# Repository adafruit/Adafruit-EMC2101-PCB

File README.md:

## Adafruit EMC2101 Tempature Sensor and Fan Controller PCB

<a href="http://www.adafruit.com/products/4808"><br/>
Click here to purchase one from the Adafruit shop</a>

PCB files for the Adafruit EMC2101 Tempature Sensor and Fan Controller. 

Format is EagleCAD schematic and board layout
* https://www.adafruit.com/product/4808

### Description

Cooling fans. They're everywhere, and they serve the important purpose of keeping things cool, generally electronics. One might rightfully think: "these fans are pretty good at moving air to keep things cool; maybe I can use one of these neat computer fans to keep my widget frosty" followed closely by throwing up one's hands in confusion at the sight of a 3 or even 4-pin connector. OK, power takes two pins but what are these other pins for and how do I use them to convince this fan to keep my things chilly?

The EMC2101 from Microchip/SMSC is a 1 degree C accurate fan controller with temperature monitoring and it will take care of all of that for you. Those extra pins allow you to set a the speed of the fan, and in the additional pin of a 4-pin connector adds a tachometer output that allows you (or the EMC2101) to monitor the speed of the fan to make sure it's working as expected. In addition to allowing you to control a fan, the EMC2101 includes an internal temperature sensor, as well as connections for an external temperature sensing diode. If you use an external temperature sensor, you can even configure a look up table (LUT) that allows you to set different fan speeds depending on the temperature, and the EMC2101 will automatically adjust the speed depending on the temperature.

This neat little chip can easily be used to help provide cooling or ventilation to your next project. You might even be able to use it to help quiet down an existing project or hack a noisy piece of electronics that has a loud fan. By allowing you to run a fan at slower speeds when cooling needs are moderate, the EMC2101 can help ease the noise pollution caused by fans running at full speed.

Delivered to you on our custom Stemma QT form factor PCB, the Adafruit EMC2101 breakout is ready to help you integrate a fan into your project by making it easy to use with a range of devices. A voltage regulator and 5V tolerant pins allow you to use it with 3.3V or 5V microcontrollers or single board computers. The included included SparkFun qwiic compatible STEMMA QT connectors for the I2C bus allow you to make easy solderless connections to your controlling device, and the standard headers make breadboard prototyping easy.Our libraries, wiring diagrams, and example code for Arduino, CircuitPython and Python complete the package. Fantastic!

### License

Adafruit invests time and resources providing this open source design, please support Adafruit and open-source hardware by purchasing products from [Adafruit](https://www.adafruit.com)!

Designed by Limor Fried/Ladyada for Adafruit Industries.

Creative Commons Attribution/Share-Alike, all text above must be included in any redistribution. 
See license.txt for additional details.

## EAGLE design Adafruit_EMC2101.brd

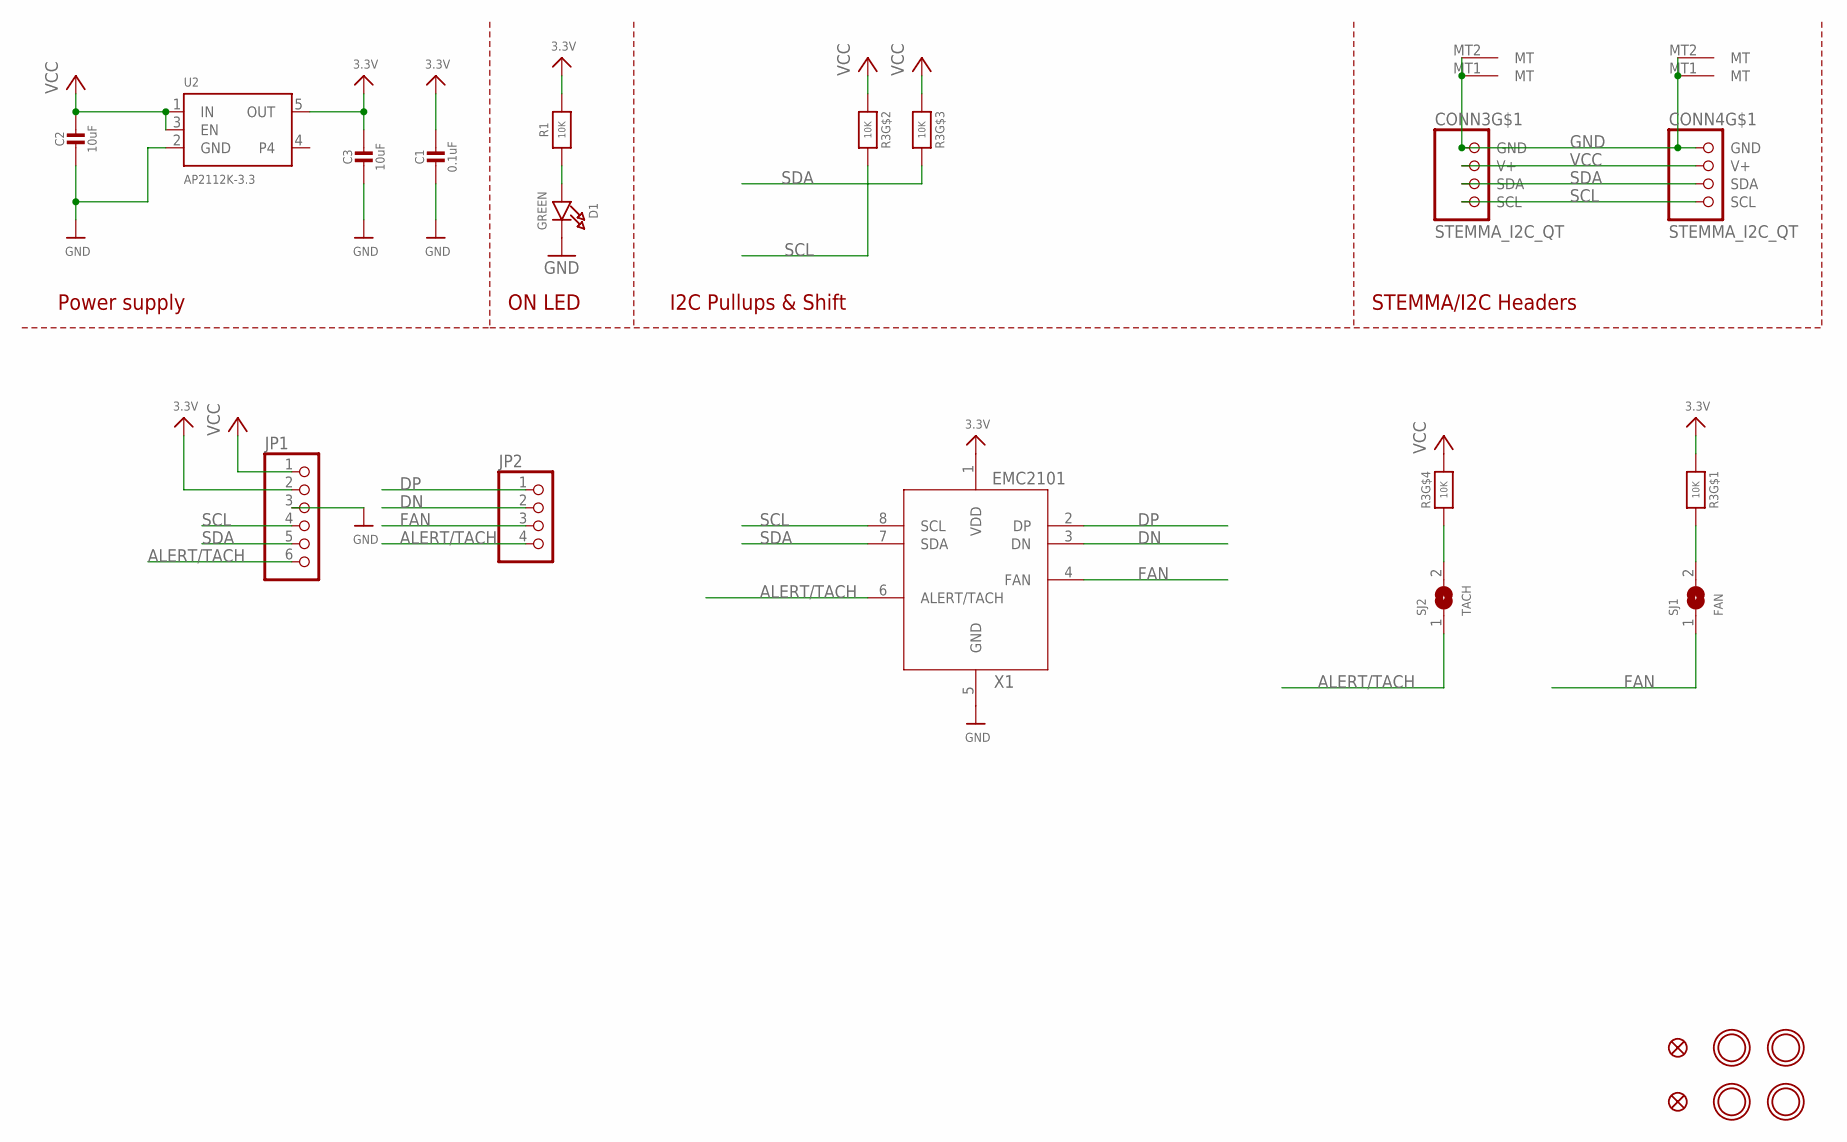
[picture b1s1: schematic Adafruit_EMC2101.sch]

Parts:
C1: 0.1uF; 0603-NO
C2, C3: 10uF; 0805-NO
CONN3, CONN4: STEMMA_I2C_QT; JST_SH4
D1: GREEN; CHIPLED_0603_NOOUTLINE
FID3, FID4: FIDUCIAL_1MM
JP1: HEADER-1X670MIL; 1X06_ROUND_70
JP2: HEADER-1X4ROUND; 1X04_ROUND
R1: 10K; _0603MP
R3: 10K; RESPACK_4X0603
SJ1: FAN; SOLDERJUMPER_CLOSEDWIRE
SJ2: TACH; SOLDERJUMPER_ARROW_NOPASTE
U2: AP2112K-3.3; SOT23-5
U$1, U$17, U$19, U$21: MOUNTINGHOLE2.5; MOUNTINGHOLE_2.5_PLATED
X1: EMC2101-AZCL; MSOP8_0.65MM

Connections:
3.3V: C1.1, C3.1, JP1.2, R1.2, R3.1, U2.5 (OUT), X1.1 (VDD)
ALERT/TACH: JP1.6, JP2.4, SJ2.1, X1.6 (ALERT/TACH)
DN: JP2.2, X1.3 (DN)
DP: JP2.1, X1.2 (DP)
FAN: JP2.3, SJ1.1, X1.4 (FAN)
GND: C1.2, C2.2, C3.2, CONN3.1 (GND), CONN3.MT1 (MT), CONN3.MT2 (MT), CONN4.1 (GND), CONN4.MT1 (MT), CONN4.MT2 (MT), D1.C, JP1.3, U2.2 (GND), X1.5 (GND)
unnamed: R3.4 (1), SJ2.2
unnamed: R3.8 (2), SJ1.2
unnamed: D1.A, R1.1
SCL: CONN3.4 (SCL), CONN4.4 (SCL), JP1.4, R3.7 (2), X1.8 (SCL)
SDA: CONN3.3 (SDA), CONN4.3 (SDA), JP1.5, R3.6 (2), X1.7 (SDA)
VCC: C2.1, CONN3.2 (V+), CONN4.2 (V+), JP1.1, R3.2 (1), R3.3 (1), R3.5 (2), U2.1 (IN), U2.3 (EN)

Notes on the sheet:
I2C Pullups & Shift
STEMMA/I2C Headers
ON LED
Power supply

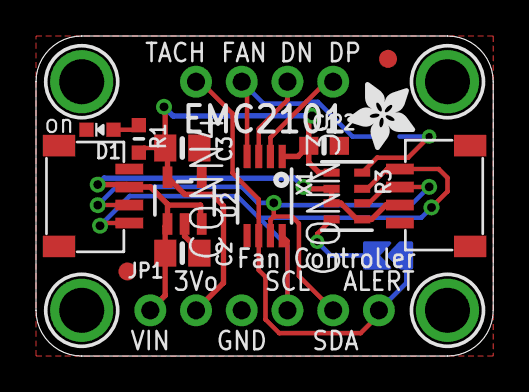
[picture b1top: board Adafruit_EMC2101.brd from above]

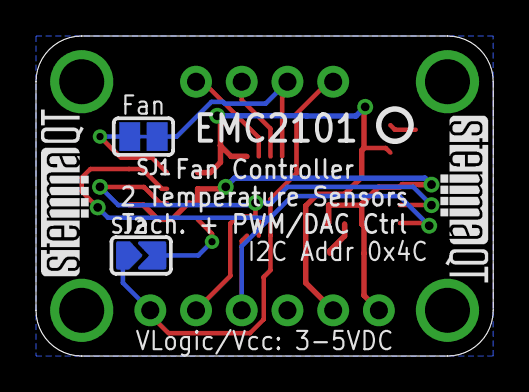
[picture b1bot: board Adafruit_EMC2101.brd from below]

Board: 2 copper layers, 25.4 x 17.8 mm, 24 parts (5 on the bottom side), 12 nets.

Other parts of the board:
U$22: ADAFRUIT_3.5MM
U$25: PCBFEAT-REV-040
U$30, U$31: STEMMAQT

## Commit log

2020-12-11 initial commit of rev b

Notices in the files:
parts and their libraries:
microbuilder: This work is placed in the public domain, and may be freely used for commercial and non-commercial work with the following conditions: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
